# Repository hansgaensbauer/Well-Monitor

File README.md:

# Well Monitor
Well monitoring equipment for Engineers Without Borders

This hardware is for projects that require more monitoring than is possible with manual measurements taken by community members. The well monitor works by weighing a pipe or other weight suspended within the well, since the apparent weight of the pipe is directly proportional to the amount of the pipe left above water.

## Installation and Use
The well monitor consists of two parts: a small "probe" that contains the load cell for weighing the pipe, and a separate box with the battery, USB flash drive, and readout electronics that gets mounted nearby. The probe requires a 3/8" hole to be drilled in the well cap over the location where the pipe is to be suspended. Remove one of the acetyl nuts on the bottom of the probe, thread the stainless-steel cable through the hole in the well cap, and reattach the nut on the other side to secure the probe. Mount the electronics box vertically against a wall or to a pole driven into the ground nearby. 

Since each well installation is different, the well monitor needs to be calibrated during installation:
1. Estimate the amount of pipe required to span the maximum expected variation in water level.
2. Calculate the maximum expected weight. This is the weight of the pipe and the cable used to suspend the pipe
3. Calculate the minimum expected weight. Calculate the buoyant force on the pipe with the water level at its highest expected level, and subtract this from the maximum weight.
4. Fill jugs of water to create "dummy" weights equal to the maximum and minimum weights, and one more equal to the difference between the maximum and minimum weights.
5. Disconnect the battery for the well monitor and remove the plastic cover that covers the electronics within the waterproof box.
6. Using clip leads, apply 9V to the indicated positions on the well monitor.
7. Use a multimeter to measure the voltage on the "Vout" testpoint indicated in the diagram.
8. Turn the "gain" potentiometer all the way to the left (counterclockwise).
9. Turn the "bias" potentiometer until the voltage on the multimeter just begins to increase above zero. Try to get the potentiometer to the very edge of the point where the voltage begins to increase.
10. Suspend the "difference" weight dummy from the well monitor. Ajust the "gain" potentiometer until the voltage reads close to 3.3V (it is clamped so that it cannot exceed this voltage).
11. Suspend the "minimum" weight dummy from the well monitor. Repeat step 9 to set the proper "zero weight" point.
12. Suspend the "maximum" weight dummy from the well monitor. The voltage should be near 3.3V. Make small adjustments to the gain and offset so that the voltage is as close as possible to zero when the minimum weight is attached, and as close as possible to 3.3V when the maximum weight is attached.

Once the battery is connected, measurements are saved once every three hours to a USB flash drive. To read the data, remove the flash drive and connect it to a computer. The file 'welldata.txt' will contain one line for each measurement, consisting of a measurement counter (to keep track of when measurements are restarted) followed by the measurement. The measurements are in "ADC Counts": a reading of 0 corresponds to zero volts, or the maximum water level when the well monitor is calibrated. A value of 32768 corresponds to 3.3V, or the minimum water level when the well monitor is calibrated.

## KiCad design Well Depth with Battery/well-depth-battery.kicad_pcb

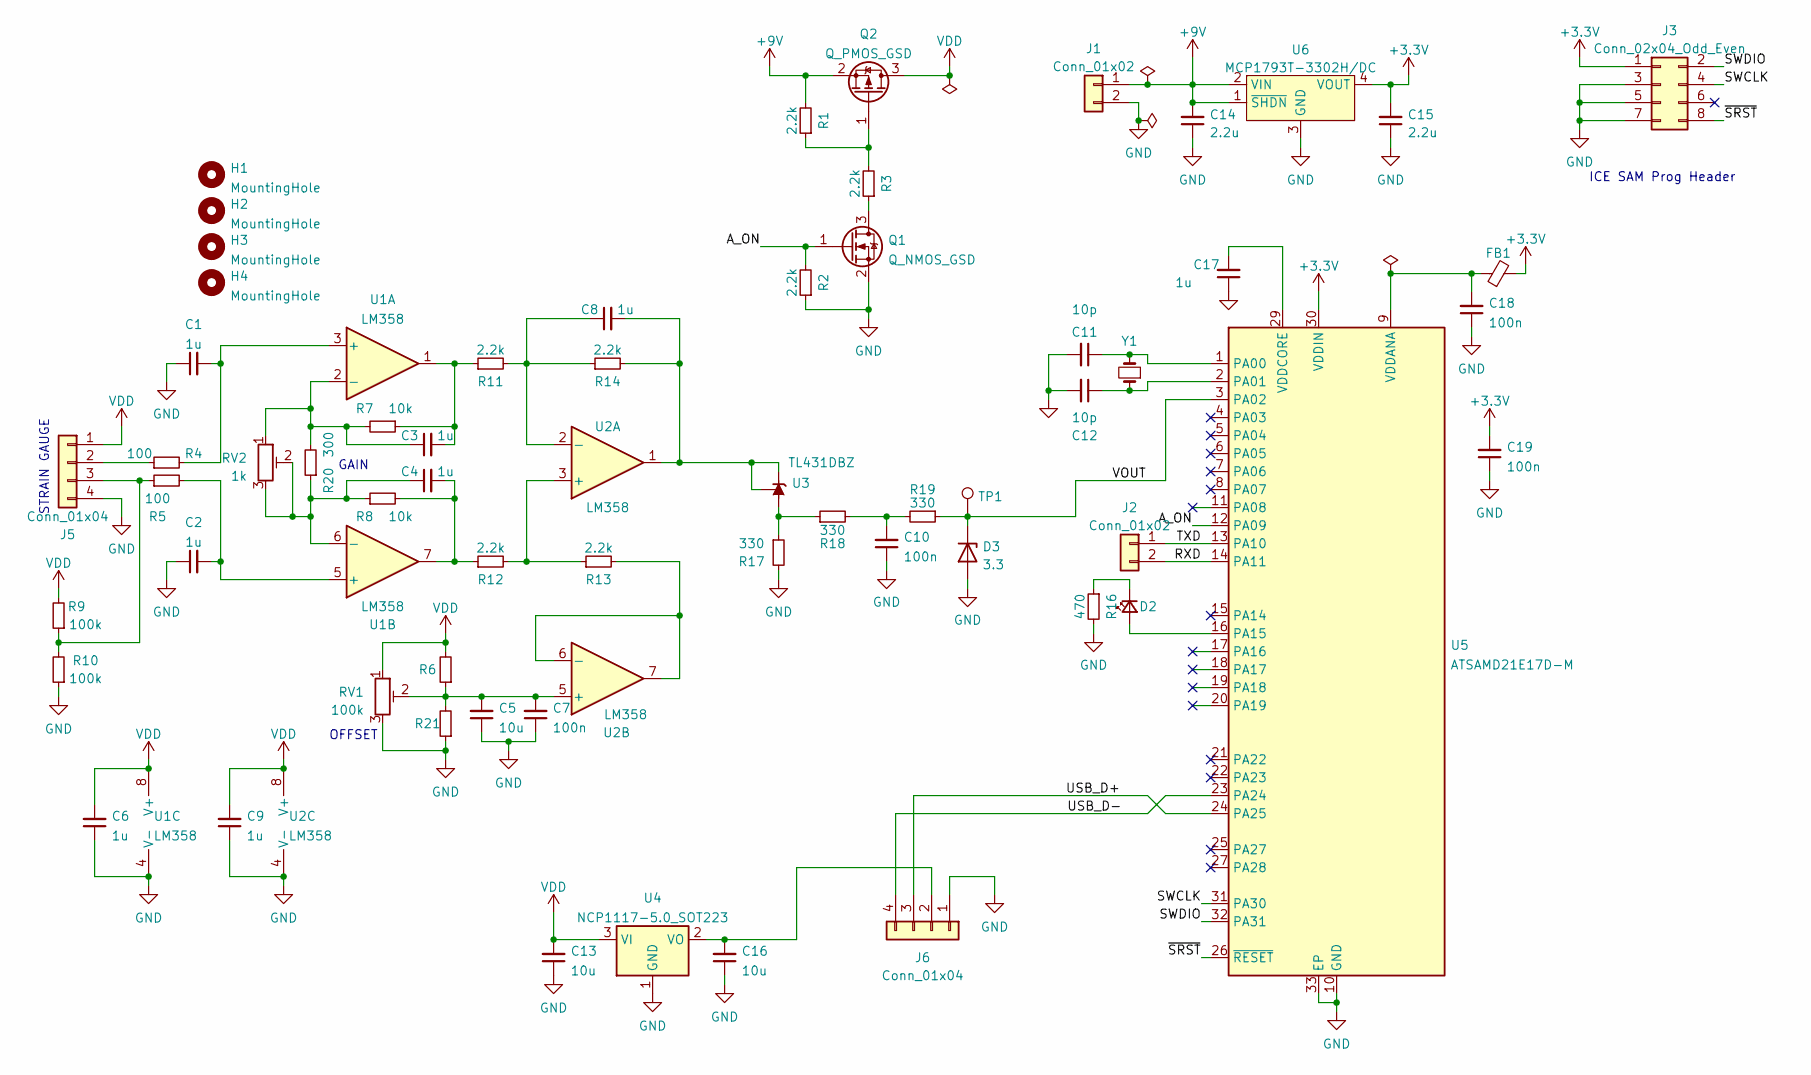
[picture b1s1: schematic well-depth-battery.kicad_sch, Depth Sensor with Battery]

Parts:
C1, C2, C3, C4, C6, C8, C9, C17: 1u; C_0603_1608Metric
C5: 10u; C_0603_1608Metric
C7, C10, C18, C19: 100n; C_0603_1608Metric
C11, C12: 10p; C_0603_1608Metric
C13, C16: 10u; C_0805_2012Metric
C14, C15: 2.2u; C_0603_1608Metric
D2: LED_Small; LED_0805_2012Metric
D3: 3.3; D_SOD-323
FB1: FerriteBead_Small; R_0603_1608Metric
H1, H2, H3, H4: MountingHole; MountingHole_3.2mm_M3
J1, J2: Conn_01x02; PinHeader_1x02_P2.54mm_Vertical
J3: Conn_02x04_Odd_Even; CardEdge_Prog
J5: Conn_01x04; PinHeader_1x04_P2.54mm_Vertical
J6: Conn_01x04; PinHeader_2x02_P2.54mm_Vertical
Q1: Q_NMOS_GSD; SOT-23
Q2: Q_PMOS_GSD; SOT-23
R1, R2, R3, R11, R12, R13, R14: 2.2k; C_0603_1608Metric
R4, R5: 100; C_0603_1608Metric
R6, R21: C_0603_1608Metric
R7, R8: 10k; C_0603_1608Metric
R9, R10: 100k; C_0603_1608Metric
R16: 470; C_0603_1608Metric
R17, R18, R19: 330; C_0603_1608Metric
R20: 300; C_0603_1608Metric
RV1: 100k; Potentiometer_Bourns_3314J_Vertical
RV2: 1k; Potentiometer_Bourns_3314J_Vertical
TP1: TestPoint; TestPoint_THTPad_1.5x1.5mm_Drill0.7mm
U1, U2: LM358; SOP-8_3.9x4.9mm_P1.27mm
U3: TL431DBZ; SOT-23
U4: NCP1117-5.0_SOT223; SOT-223-3_TabPin2
U5: ATSAMD21E17D-M; QFN-32-1EP_5x5mm_P0.5mm_EP3.6x3.6mm
U6: MCP1793T-3302H/DC; SOT-223-6
Y1: Crystal_Small; Crystal_SMD_MicroCrystal_CM9V-T1A-2Pin_1.6x1.0mm

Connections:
+3.3V: C15.2, C19.2, FB1.2, J3.1, U5.30 (VDDIN), U6.4 (VOUT)
+9V: C14.2, J1.1, Q2.2 (S), R1.2, U6.1 (~SHDN), U6.2 (VIN)
/A_ON: Q1.1 (G), R2.2, U5.12 (PA09)
/RXD: J2.2, U5.14 (PA11)
/SWCLK: J3.4, U5.31 (PA30)
/SWDIO: J3.2, U5.32 (PA31)
/TXD: J2.1, U5.13 (PA10)
/USB_D+: J6.3, U5.24 (PA25)
/USB_D-: J6.4, U5.23 (PA24)
/VOUT: D3.1 (K), R19.1, TP1.1, U5.3 (PA02)
/~SRST: J3.8, U5.26 (~RESET)
GND: C1.1, C2.1, C5.1, C6.1, C7.1, C9.1, C10.1, C11.2, C12.2, C13.1, C14.1, C15.1, C16.1, C17.1, C18.1, C19.1, D3.2 (A), J1.2, J3.3, J3.5, J3.7, J5.4, J6.1, Q1.2 (S), R2.1, R10.1, R16.2, R17.2, R21.1, RV1.3, U1.4 (V-), U2.4 (V-), U4.1 (GND), U5.10 (GND), U5.28 (GND), U5.33 (EP), U6.3 (GND), U6.6 (GND)
unnamed: C3.2, R7.1, R11.1, U1.1
unnamed: C4.2, R8.2, R12.1, U1.7
unnamed: C10.2, R18.2, R19.2
unnamed: D2.2 (A), U5.16 (PA15)
unnamed: D2.1 (K), R16.1
unnamed: J5.2, R4.1
unnamed: J5.3, R5.1, R9.1, R10.2
unnamed: C16.2, J6.2, U4.2 (VO)
unnamed: Q1.3 (D), R3.1
unnamed: Q2.1 (G), R1.1, R3.2
unnamed: C1.2, R4.2, U1.3 (+)
unnamed: C3.1, R7.2, R20.2, RV2.1, U1.2 (-)
unnamed: C2.2, R5.2, U1.5 (+)
unnamed: C4.1, R8.1, R20.1, RV2.2, RV2.3, U1.6 (-)
unnamed: R12.2, R13.1, U2.3 (+)
unnamed: C8.1, R11.2, R14.1, U2.2 (-)
unnamed: C5.2, C7.2, R6.1, R21.2, RV1.2, U2.5 (+)
unnamed: R13.2, U2.6 (-), U2.7
unnamed: R17.1, R18.1, U3.3 (A)
unnamed: C8.2, R14.2, U2.1, U3.1 (K), U3.2 (REF)
unnamed: C11.1, U5.1 (PA00), Y1.2
unnamed: C12.1, U5.2 (PA01), Y1.1
unnamed: C18.2, FB1.1, U5.9 (VDDANA)
unnamed: C17.2, U5.29 (VDDCORE)
VDD: C6.2, C9.2, C13.2, J5.1, Q2.3 (D), R6.2, R9.2, RV1.1, U1.8 (V+), U2.8 (V+), U4.3 (VI)

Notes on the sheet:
GAIN
OFFSET
STRAIN GAUGE
ICE SAM Prog Header

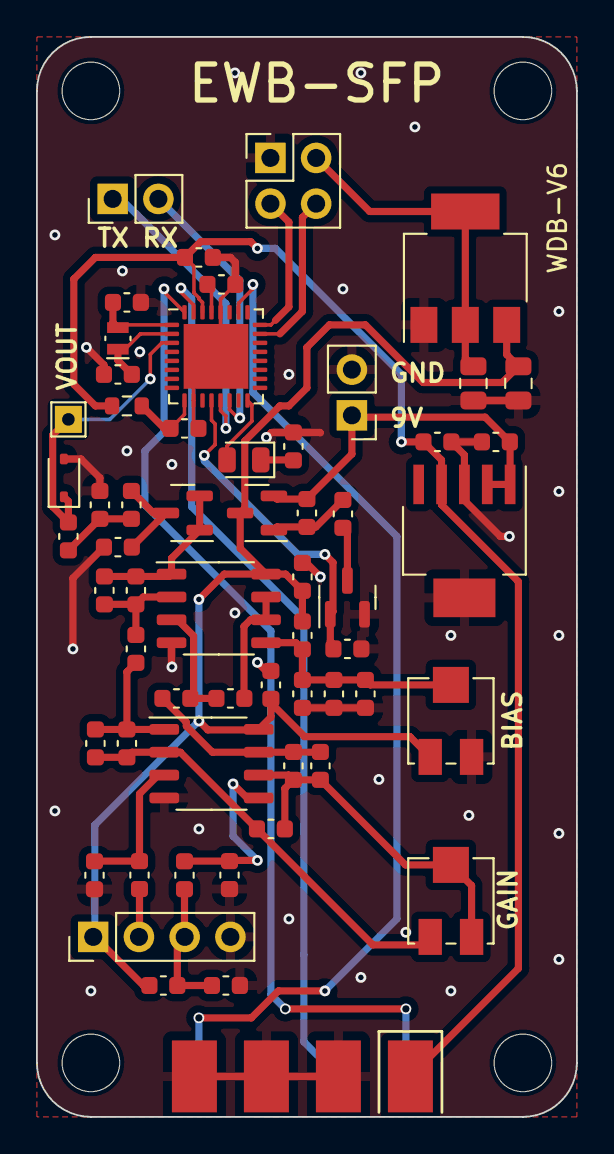
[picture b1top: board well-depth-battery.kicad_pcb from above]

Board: 2 copper layers, 30.0 x 60.0 mm, 63 parts (0 on the bottom side), 37 nets.

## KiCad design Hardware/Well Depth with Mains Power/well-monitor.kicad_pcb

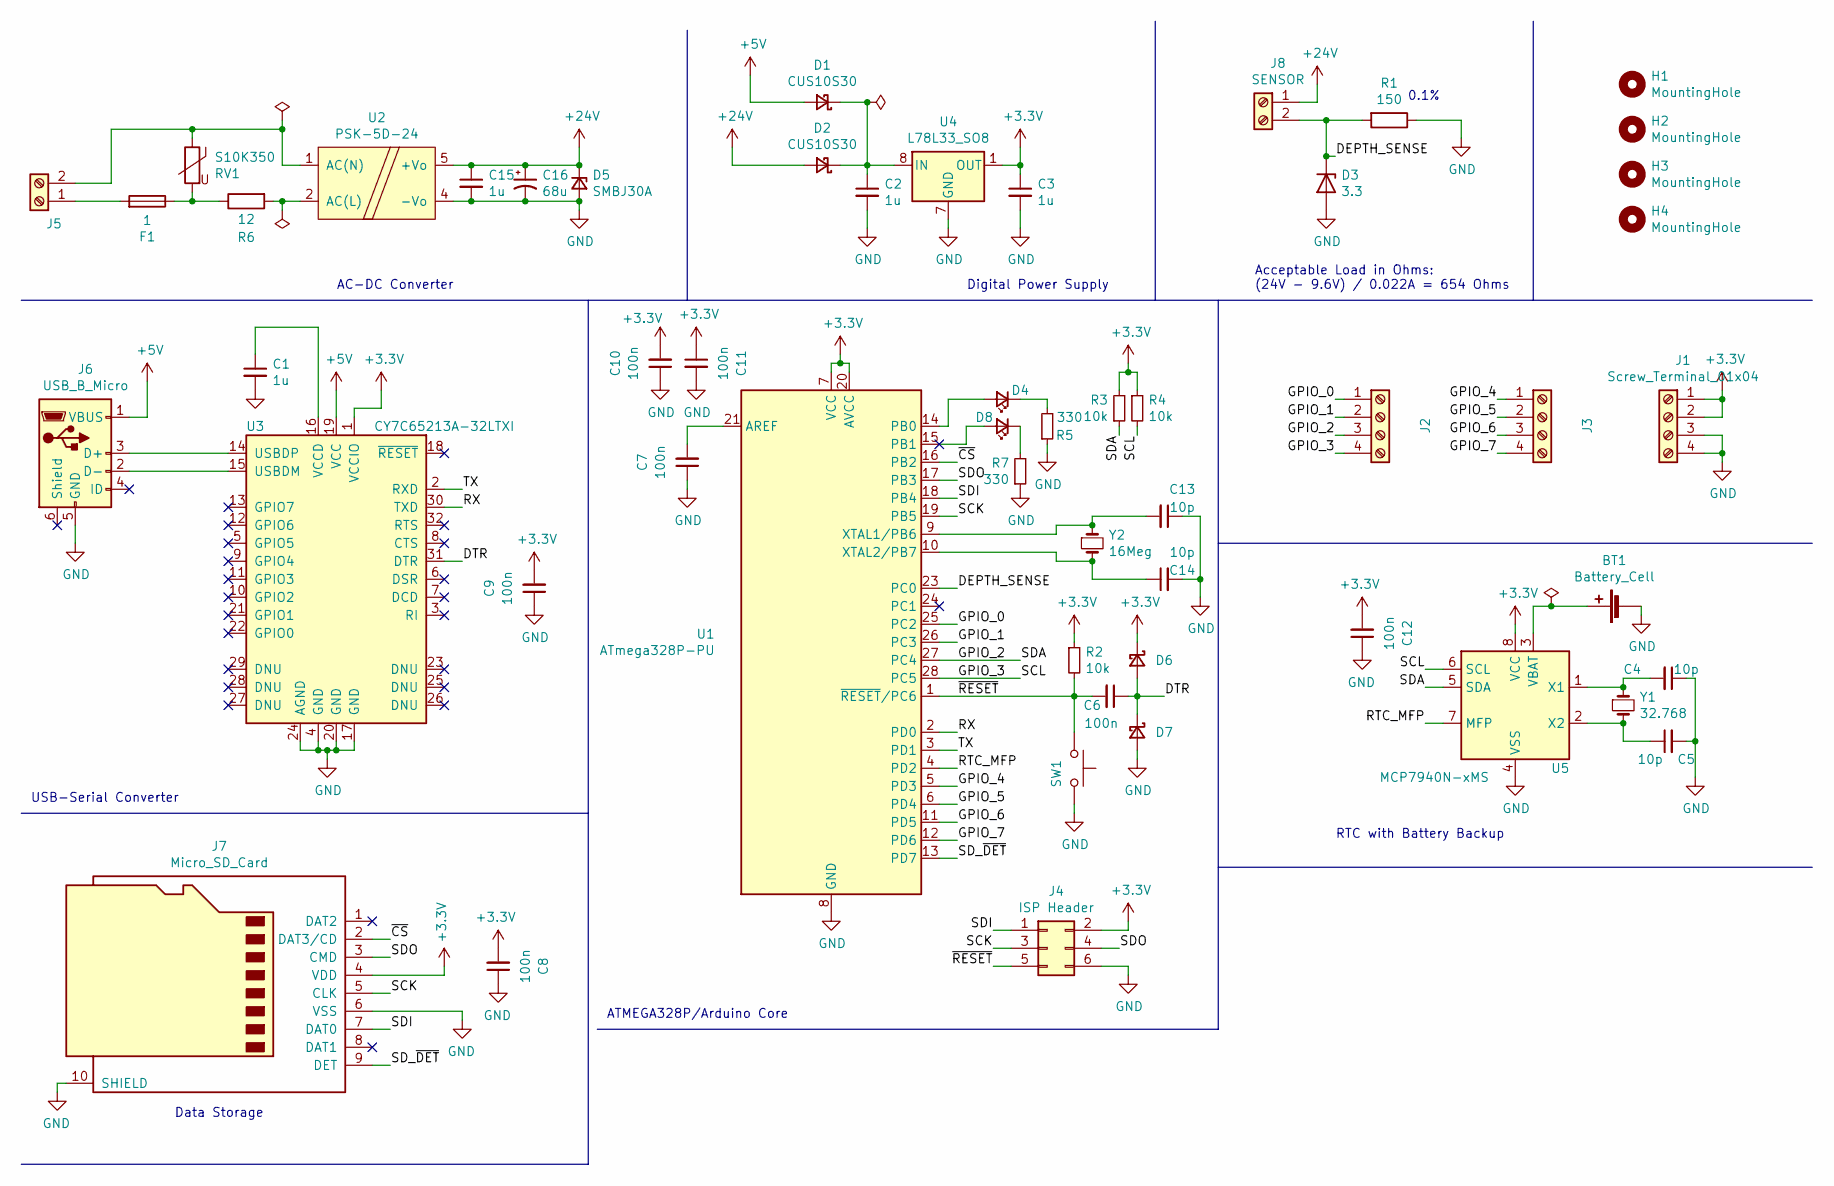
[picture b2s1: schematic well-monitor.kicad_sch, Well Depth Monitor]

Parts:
BT1: Battery_Cell; BatteryHolder_Keystone_3002_1x2032
C1, C2, C3: 1u; C_0603_1608Metric
C4, C5, C13, C14: 10p; C_0603_1608Metric
C6, C7, C8, C9, C10, C11, C12: 100n; C_0603_1608Metric
C15: 1u; C_1206_3216Metric
C16: 68u; CP_Radial_D10.0mm_P5.00mm
D1, D2, D6, D7: CUS10S30; D_SOD-323
D3: 3.3; D_SOD-123
D4, D8: LED_Small; LED_0603_1608Metric
D5: SMBJ30A; D_SMB
F1: 1; Fuse_1206_3216Metric
H1, H2, H3, H4: MountingHole; MountingHole_3.2mm_M3
J1, J2, J3: Screw_Terminal_01x04; TerminalBlock_Phoenix_PT-1,5-4-5.0-H_1x04_P5.00mm_Horizontal
J4: ISP Header; PinHeader_2x03_P2.54mm_Vertical
J5: Screw_Terminal_01x02; TerminalBlock_Phoenix_PT-1,5-2-5.0-H_1x02_P5.00mm_Horizontal
J6: USB_B_Micro; USB_Micro-B_GCT_USB3076-30-A
J7: Micro_SD_Card; MEM2051-00-195-00-A
J8: SENSOR; TerminalBlock_Phoenix_PT-1,5-2-5.0-H_1x02_P5.00mm_Horizontal
R1: 150; R_0603_1608Metric
R2, R3, R4: 10k; R_0603_1608Metric
R5, R7: 330; R_0603_1608Metric
R6: 12; R_Axial_DIN0614_L14.3mm_D5.7mm_P20.32mm_Horizontal
RV1: S10K350; RV_Disc_D12mm_W5.4mm_P7.5mm
SW1: SW_Push; PTS636-SP43-LFS
U1: ATmega328P-PU; DIP-28_W7.62mm
U2: PSK-5D-24
U3: CY7C65213A-32LTXI; QFN-32-1EP_5x5mm_P0.5mm_EP3.45x3.45mm
U4: L78L33_SO8; SOIC-8_3.9x4.9mm_P1.27mm
U5: MCP7940N-xMS; MSOP-8_3x3mm_P0.65mm
Y1: 32.768; Crystal_SMD_MicroCrystal_CM9V-T1A-2Pin_1.6x1.0mm
Y2: 16Meg; Crystal_HC49-U_Vertical

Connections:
+3V3: C3.1, C8.2, C9.2, C10.2, C11.1, C12.2, D6.1 (K), J1.1, J1.2, J4.2, J7.4 (VDD), R2.1, R3.2, R4.1, U1.7 (VCC), U1.20 (AVCC), U3.1 (VCCIO), U4.1 (OUT), U5.8 (VCC)
+5V: D1.2 (A), J6.1 (VBUS), U3.19 (VCC)
+24V: C15.1, C16.1, D2.2 (A), D5.1 (K), J8.1, U2.5 (+Vo)
/DEPTH_SENSE: D3.1 (K), J8.2, R1.2, U1.23 (PC0)
/DTR: C6.1, D6.2 (A), D7.1 (K), U3.31 (DTR)
/GPIO_0: J2.1, U1.25 (PC2)
/GPIO_1: J2.2, U1.26 (PC3)
/GPIO_2: J2.3, R3.1, U1.27 (PC4), U5.5 (SDA)
/GPIO_3: J2.4, R4.2, U1.28 (PC5), U5.6 (SCL)
/GPIO_4: J3.1, U1.5 (PD3)
/GPIO_5: J3.2, U1.6 (PD4)
/GPIO_6: J3.3, U1.11 (PD5)
/GPIO_7: J3.4, U1.12 (PD6)
/RTC_MFP: U1.4 (PD2), U5.7 (MFP)
/RX: U1.2 (PD0), U3.30 (TXD)
/SCK: J4.3, J7.5 (CLK), U1.19 (PB5)
/SDI: J4.1, J7.7 (DAT0), U1.18 (PB4)
/SDO: J4.4, J7.3 (CMD), U1.17 (PB3)
/SD_~DET: J7.9 (DET), U1.13 (PD7)
/TX: U1.3 (PD1), U3.2 (RXD)
/~CS: J7.2 (DAT3/CD), U1.16 (PB2)
/~RESET: C6.2, J4.5, R2.2, SW1.1, U1.1 (~RESET/PC6)
GND: BT1.2 (-), C1.2, C2.2, C3.2, C4.1, C5.2, C7.1, C8.1, C9.1, C10.1, C11.2, C12.1, C13.1, C14.2, C15.2, C16.2, D3.2 (A), D5.2 (A), D7.2 (A), J1.3, J1.4, J4.6, J6.5 (GND), J7.6 (VSS), J7.10 (SHIELD), R1.1, R5.1, R7.1, SW1.2, U1.8 (GND), U1.22 (GND), U2.4 (-Vo), U3.4 (GND), U3.17 (GND), U3.20 (GND), U3.24 (AGND), U4.2 (GND), U4.3 (GND), U4.6 (GND), U4.7 (GND), U5.4 (VSS)
unnamed: BT1.1 (+), U5.3 (VBAT)
unnamed: C1.1, U3.16 (VCCD)
unnamed: C2.1, D1.1 (K), D2.1 (K), U4.8 (IN)
unnamed: C4.2, U5.1 (X1), Y1.1
unnamed: C5.1, U5.2 (X2), Y1.2
unnamed: C7.2, U1.21 (AREF)
unnamed: C13.2, U1.9 (XTAL1/PB6), Y2.1
unnamed: C14.1, U1.10 (XTAL2/PB7), Y2.2
unnamed: D4.1 (K), R5.2
unnamed: D4.2 (A), U1.14 (PB0)
unnamed: D8.1 (K), R7.2
unnamed: D8.2 (A), U1.15 (PB1)
unnamed: F1.1, R6.1, RV1.2
unnamed: F1.2, J5.1
unnamed: J5.2, RV1.1, U2.1 (AC(N))
unnamed: J6.2 (D-), U3.15 (USBDM)
unnamed: J6.3 (D+), U3.14 (USBDP)
unnamed: R6.2, U2.2 (AC(L))

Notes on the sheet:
RTC with Battery Backup
USB-Serial Converter
Data Storage
AC-DC Converter
Digital Power Supply
Acceptable Load in Ohms: (24V - 9.6V) / 0.022A = 654 Ohms
0.1%
ATMEGA328P/Arduino Core

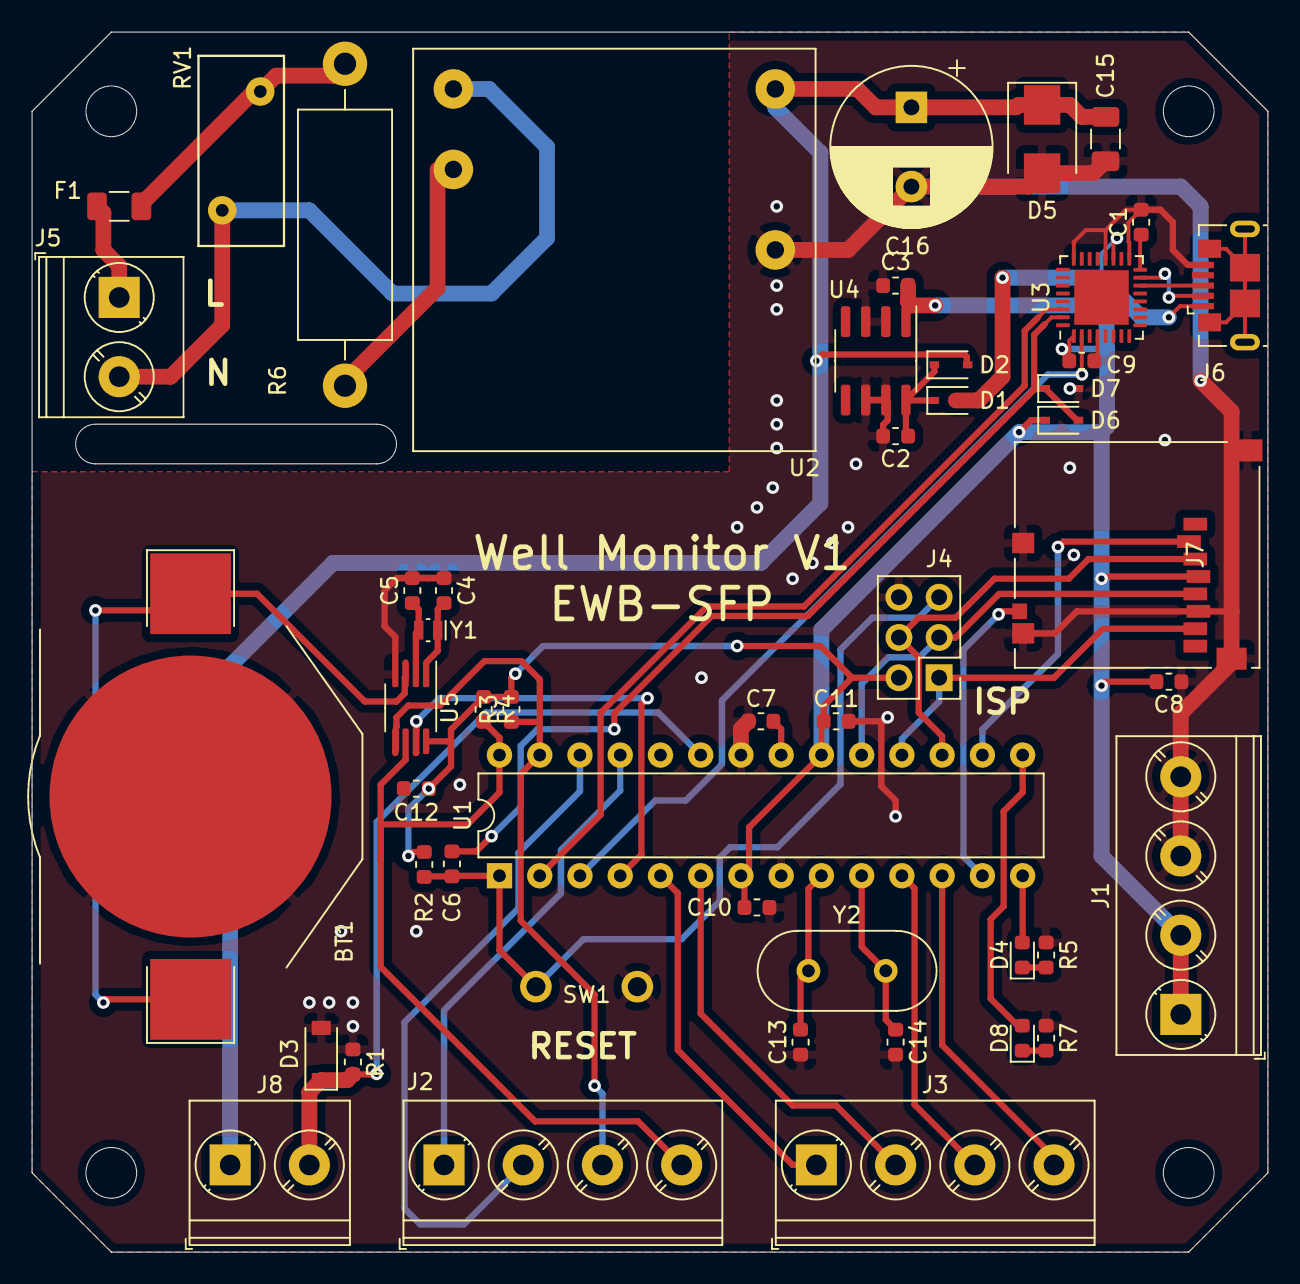
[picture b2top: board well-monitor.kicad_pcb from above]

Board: 2 copper layers, 78.0 x 77.0 mm, 54 parts (0 on the bottom side), 41 nets.

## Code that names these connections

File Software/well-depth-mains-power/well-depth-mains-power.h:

/*
 * Engineers Without Borders San Francisco Professional Chapter
 * 
 * Well Monitor Firmware with well depth sensing and mains power
 * 
 * See https://github.com/hansgaensbauer/Well-Monitor
 */

 #ifndef WDMP_H_
 #define WDMP_H_

  //Pin connections
  #define LEDPIN 8
  #define DEPTH_SENSE_INPUT A0
  #define GPIO_0 A2
  #define GPIO_1 A3
  #define GPIO_2 A4
  #define GPIO_3 A5
  #define GPIO_4 3
  #define GPIO_5 4
  #define GPIO_6 5
  #define GPIO_7 6
  #define SD_DET_N 7
  #define SD_CS_N 10
  #define RTC_MFP 2

  #define PRESSURE_RANGE 100 //maximum measurable pressure in psi
  #define SENSE_RESISTANCE 150.0
  #define VCC 3.3
  #define ADC_BITS 1023.0
  #define ZERO_SCALE_CURRENT 0.004
  #define FULL_SCALE_CURRENT 0.020

  #define PSI_TO_MH2O 0.703070

 #endif //WDMP_H_

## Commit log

2021-11-02 First Pass Schematic
2021-11-02 Moved libraries to lib folder
2021-11-03 First pass routing and DRC/ERC pass
2021-11-03 Update README with device photos
2021-11-10 Received hardware, started implementing software
    Arduino IDE compatibility works, and SD card data logging has been tested and is functional.
2021-11-11 V1 (Fix issues with V0)
2021-11-12 Created arduino-style pinout
2021-11-12 Started installation documentation
2021-11-12 Added RTC functionality
2022-02-09 Well Monitor: Update to newest KiCAD version
    Also updated CAM files
2022-02-09 Depth Sensor: Add depth sensor simulations
    Basic simulations to confirm the general behavior of the depth sensor INA
2022-02-09 Depth Sensor: Create Schematic
    Created KiCAD schematic for the depth sensor amplifier
2022-02-09 Depth Sensor: Add KiCAD files
2022-02-09 Depth-Sensor: Routing and PCB layout
    Also update .gitignore to KiCAD 6
2022-02-09 Depth Sensor: CAM
    Also fixed folder structure
2022-02-09 Depth Sensor: Create zip for fab
2022-02-09 Project: remove obsolete copies from directory
2022-02-10 WDMP: Add photo of assembled hardware
2022-02-26 Simulation: Add Solar Simulator
2022-04-06 Well Depth Battery: Create Schematic
    Schematic ERC pass.
2022-04-07 Project: Rearrange the Project
    Move all different devices to their own high-level folders.
2022-04-08 WDB: Floorplanning
    Also fixed .gitignore to not ignore lib
2022-04-08 Project: Fix KiCAD libraries
2022-04-09 WDB: New Board Outline
2022-04-09 WDB: Layout and CAM
2022-04-18 Add photos of WDB assembly
2022-04-18 Add WDB photos to README
2022-05-03 Start WDB Refactor w/ SAMD21
2022-05-04 WDB: ERC Pass
2022-05-04 WDB: DRC Pass and Fab
2022-06-14 WDB-Firmware: Create Project
    Also update .gitignore
2022-06-20 Fix wdb Firmware Project
    Compiles, blinks LED
2022-06-20 FW: Draft USART Init
2022-06-20 FW: USART Compiles
2022-06-20 FW: UART Working
2022-06-21 FW: ADC Setup Complete
2022-06-21 FW: ADC Driver Works
2022-06-22 FW: Clock config for MSC
2022-06-22 FW: Eliminate clock side effects
2022-06-22 FW: Add USB MSC and Tweak Config
2022-06-22 FW: Add SOF Callback
2022-06-22 FW: Add FatFS and test code
2022-06-22 FW: Reading from USB
2022-06-22 FW: Move USB Code to usb_flash files
2022-06-22 FW: Remove SOF Callback
2022-06-22 FW: USB MSC Datalogging Works!
2022-06-23 FW: Draft RTC Driver (nonfunctional)
2022-06-23 FW: Fix RTC Driver
    Interrupts working
2022-06-26 Doc: Create Manual
2022-06-26 Doc: Add Manual PDF
2022-06-28 FW: Fix .gitignore to include /instance folder
2022-06-28 FW: UHC Causes RTC Problem
2022-06-28 FW: Firmware works
    Saving data every 10 seconds
2023-05-11 removed sd card
2023-05-11 First pass routing for rectangular board
2023-05-13 redo routing, DRC/ERC pass
2023-05-13 Fix prog connector
2023-12-03 Remove old well monitor versions to prioritize WDB-V6
2023-12-03 Add mechanical components, move firmware
2023-12-03 Add photos
2023-12-03 Add packaging designs
2023-12-03 Rotate photos and add diagrams
2023-12-03 Update README.md, make photos smaller
2023-12-03 Fix whitespace in calibration diagram
2023-12-03 Second calibration figure improvements

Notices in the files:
parts and their libraries:
Copyright 2021 Accelerated Designs. All rights reserved.
